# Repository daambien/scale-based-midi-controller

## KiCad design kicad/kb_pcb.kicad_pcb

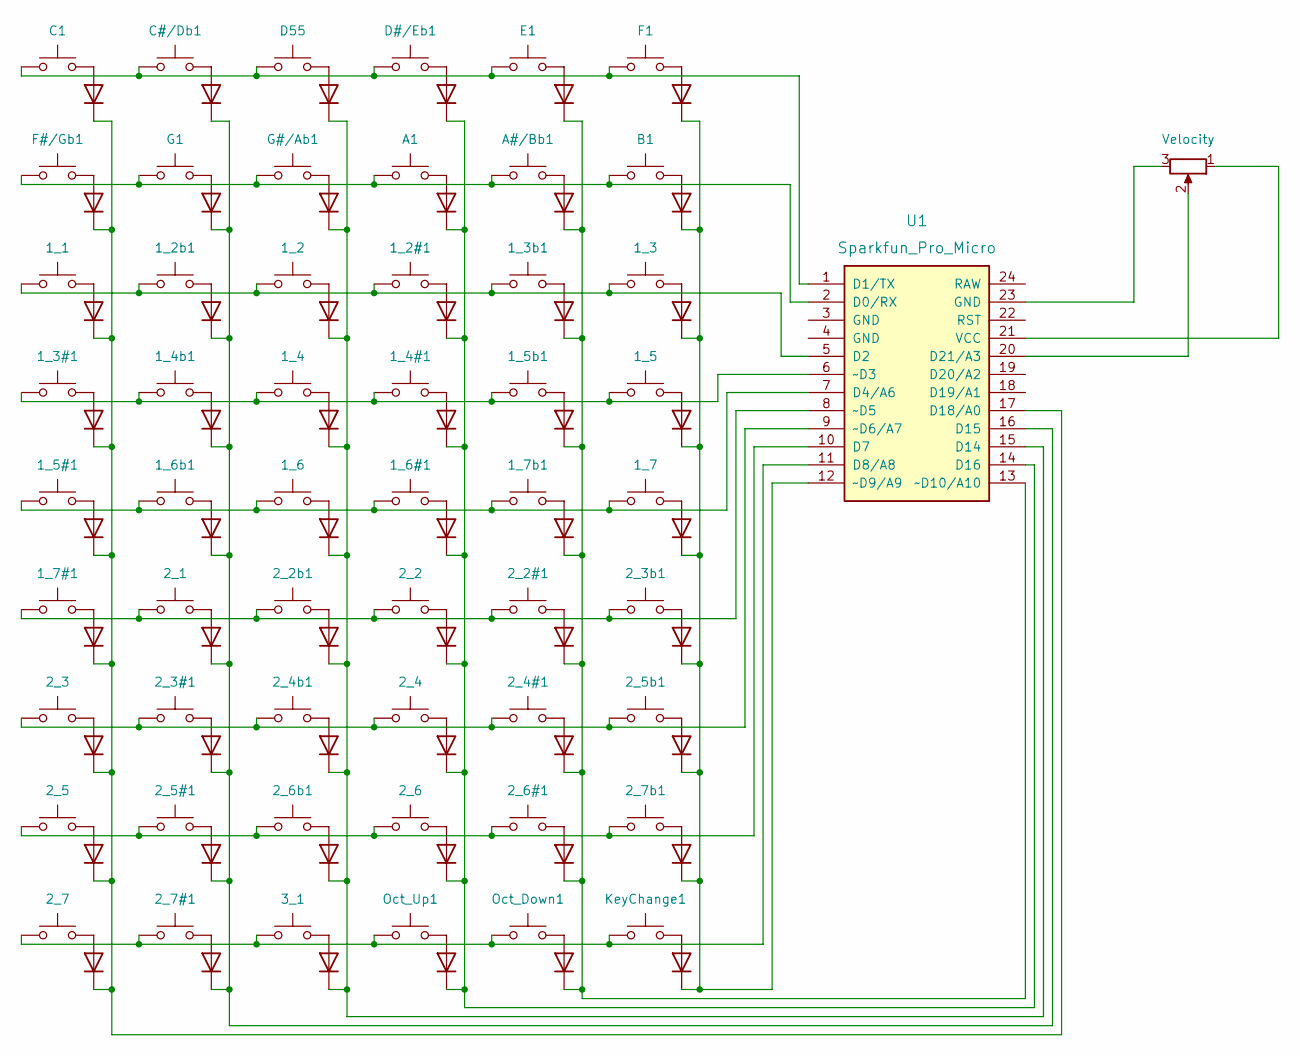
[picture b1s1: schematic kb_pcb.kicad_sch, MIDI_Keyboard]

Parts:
1_1, 1_2, 1_2#1, 1_2b1, 1_3, 1_3#1, 1_3b1, 1_4, 1_4#1, 1_4b1, 1_5, 1_5#1, 1_5b1, 1_6, 1_6#1, 1_6b1, 1_7, 1_7#1, 1_7b1, 2_1, 2_2, 2_2#1, 2_2b1, 2_3, 2_3#1, 2_3b1, 2_4, 2_4#1, 2_4b1, 2_5, 2_5#1, 2_5b1, 2_6, 2_6#1, 2_6b1, 2_7, 2_7#1, 2_7b1, 3_1: SW_Push; SW_Cherry_MX_1.00u_Plate
A1: SW_Push; SW_Cherry_MX_1.00u_Plate
A#/Bb1: SW_Push; SW_Cherry_MX_1.00u_Plate
B1: SW_Push; SW_Cherry_MX_1.00u_Plate
C1: SW_Push; SW_Cherry_MX_1.00u_Plate
C#/Db1: SW_Push; SW_Cherry_MX_1.00u_Plate
D1, D2, D3, D4, D5, D6, D7, D8, D9, D10, D11, D12, D13, D14, D15, D16, D17, D18, D19, D20, D21, D22, D23, D24, D25, D26, D27, D28, D29, D30, D31, D32, D33, D34, D35, D36, D37, D38, D39, D40, D41, D42, D43, D44, D45, D46, D47, D48, D49, D50, D51, D52, D53, D54: 1N4148; D_DO-35_SOD27_P7.62mm_Horizontal
D55: SW_Push; SW_Cherry_MX_1.00u_Plate
D#/Eb1: SW_Push; SW_Cherry_MX_1.00u_Plate
E1: SW_Push; SW_Cherry_MX_1.00u_Plate
F1: SW_Push; SW_Cherry_MX_1.00u_Plate
F#/Gb1: SW_Push; SW_Cherry_MX_1.00u_Plate
G1: SW_Push; SW_Cherry_MX_1.00u_Plate
G#/Ab1: SW_Push; SW_Cherry_MX_1.00u_Plate
KeyChange1: SW_Push; SW_Cherry_MX_1.00u_Plate
Oct_Down1: SW_Push; SW_Cherry_MX_1.00u_Plate
Oct_Up1: SW_Push; SW_Cherry_MX_1.00u_Plate
RV1: Velocity
U1: Sparkfun_Pro_Micro

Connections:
unnamed: 1_1.1, 1_2.1, 1_2#1.1, 1_2b1.1, 1_3.1, 1_3b1.1, U1.5 (D2)
unnamed: 1_1.2, D3.2 (A)
unnamed: 1_2#1.2, D30.2 (A)
unnamed: 1_2.2, D21.2 (A)
unnamed: 1_2b1.2, D12.2 (A)
unnamed: 1_3#1.1, 1_4.1, 1_4#1.1, 1_4b1.1, 1_5.1, 1_5b1.1, U1.6 (~D3)
unnamed: 1_3#1.2, D4.2 (A)
unnamed: 1_3.2, D48.2 (A)
unnamed: 1_3b1.2, D39.2 (A)
unnamed: 1_4#1.2, D31.2 (A)
unnamed: 1_4.2, D22.2 (A)
unnamed: 1_4b1.2, D13.2 (A)
unnamed: 1_5#1.1, 1_6.1, 1_6#1.1, 1_6b1.1, 1_7.1, 1_7b1.1, U1.7 (D4/A6)
unnamed: 1_5#1.2, D5.2 (A)
unnamed: 1_5.2, D49.2 (A)
unnamed: 1_5b1.2, D40.2 (A)
unnamed: 1_6#1.2, D32.2 (A)
unnamed: 1_6.2, D23.2 (A)
unnamed: 1_6b1.2, D14.2 (A)
unnamed: 1_7#1.1, 2_1.1, 2_2.1, 2_2#1.1, 2_2b1.1, 2_3b1.1, U1.8 (~D5)
unnamed: 1_7#1.2, D6.2 (A)
unnamed: 1_7.2, D50.2 (A)
unnamed: 1_7b1.2, D41.2 (A)
unnamed: 2_1.2, D15.2 (A)
unnamed: 2_2#1.2, D42.2 (A)
unnamed: 2_2.2, D33.2 (A)
unnamed: 2_2b1.2, D24.2 (A)
unnamed: 2_3.1, 2_3#1.1, 2_4.1, 2_4#1.1, 2_4b1.1, 2_5b1.1, U1.9 (~D6/A7)
unnamed: 2_3#1.2, D16.2 (A)
unnamed: 2_3.2, D7.2 (A)
unnamed: 2_3b1.2, D51.2 (A)
unnamed: 2_4#1.2, D43.2 (A)
unnamed: 2_4.2, D34.2 (A)
unnamed: 2_4b1.2, D25.2 (A)
unnamed: 2_5.1, 2_5#1.1, 2_6.1, 2_6#1.1, 2_6b1.1, 2_7b1.1, U1.10 (D7)
unnamed: 2_5#1.2, D17.2 (A)
unnamed: 2_5.2, D8.2 (A)
unnamed: 2_5b1.2, D52.2 (A)
unnamed: 2_6#1.2, D44.2 (A)
unnamed: 2_6.2, D35.2 (A)
unnamed: 2_6b1.2, D26.2 (A)
unnamed: 2_7#1.2, D18.2 (A)
unnamed: 2_7.2, D9.2 (A)
unnamed: 2_7b1.2, D53.2 (A)
unnamed: 2_7.1, 2_7#1.1, 3_1.1, KeyChange1.1, Oct_Down1.1, Oct_Up1.1, U1.11 (D8/A8)
unnamed: 3_1.2, D27.2 (A)
unnamed: A1.2, D29.2 (A)
unnamed: A1.1, A#/Bb1.1, B1.1, F#/Gb1.1, G1.1, G#/Ab1.1, U1.2 (D0/RX)
unnamed: A#/Bb1.2, D38.2 (A)
unnamed: B1.2, D47.2 (A)
unnamed: C1.2, D1.2 (A)
unnamed: C1.1, C#/Db1.1, D55.1, D#/Eb1.1, E1.1, F1.1, U1.1 (D1/TX)
unnamed: C#/Db1.2, D10.2 (A)
unnamed: D1.1 (K), D2.1 (K), D3.1 (K), D4.1 (K), D5.1 (K), D6.1 (K), D7.1 (K), D8.1 (K), D9.1 (K), U1.17 (D18/A0)
unnamed: D10.1 (K), D11.1 (K), D12.1 (K), D13.1 (K), D14.1 (K), D15.1 (K), D16.1 (K), D17.1 (K), D18.1 (K), U1.16 (D15)
unnamed: D19.1 (K), D20.1 (K), D21.1 (K), D22.1 (K), D23.1 (K), D24.1 (K), D25.1 (K), D26.1 (K), D27.1 (K), U1.15 (D14)
unnamed: D28.1 (K), D29.1 (K), D30.1 (K), D31.1 (K), D32.1 (K), D33.1 (K), D34.1 (K), D35.1 (K), D36.1 (K), U1.14 (D16)
unnamed: D37.1 (K), D38.1 (K), D39.1 (K), D40.1 (K), D41.1 (K), D42.1 (K), D43.1 (K), D44.1 (K), D45.1 (K), U1.13 (~D10/A10)
unnamed: D46.1 (K), D47.1 (K), D48.1 (K), D49.1 (K), D50.1 (K), D51.1 (K), D52.1 (K), D53.1 (K), D54.1 (K), U1.12 (~D9/A9)
unnamed: D19.2 (A), D55.2
unnamed: D28.2 (A), D#/Eb1.2
unnamed: D37.2 (A), E1.2
unnamed: D46.2 (A), F1.2
unnamed: D2.2 (A), F#/Gb1.2
unnamed: D11.2 (A), G1.2
unnamed: D20.2 (A), G#/Ab1.2
unnamed: D54.2 (A), KeyChange1.2
unnamed: D45.2 (A), Oct_Down1.2
unnamed: D36.2 (A), Oct_Up1.2
unnamed: RV1.1, U1.21 (VCC)
unnamed: RV1.2, U1.20 (D21/A3)
unnamed: RV1.3, U1.23 (GND)

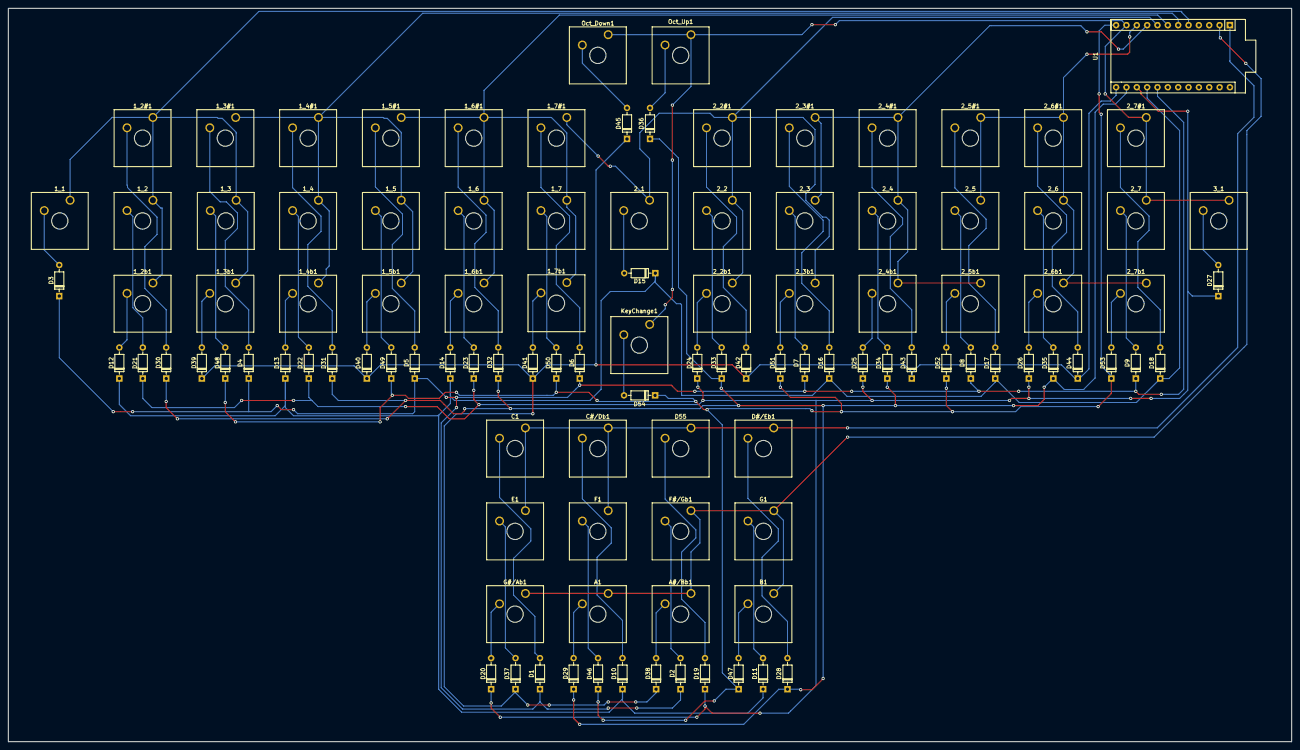
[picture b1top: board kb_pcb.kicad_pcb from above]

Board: 2 copper layers, 315.0 x 180.0 mm, 109 parts (0 on the bottom side), 69 nets.

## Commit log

2022-11-20 Initial Commit
    Just all of the files I've been working on locally.
2022-11-24 Added pitch bend soft pot
